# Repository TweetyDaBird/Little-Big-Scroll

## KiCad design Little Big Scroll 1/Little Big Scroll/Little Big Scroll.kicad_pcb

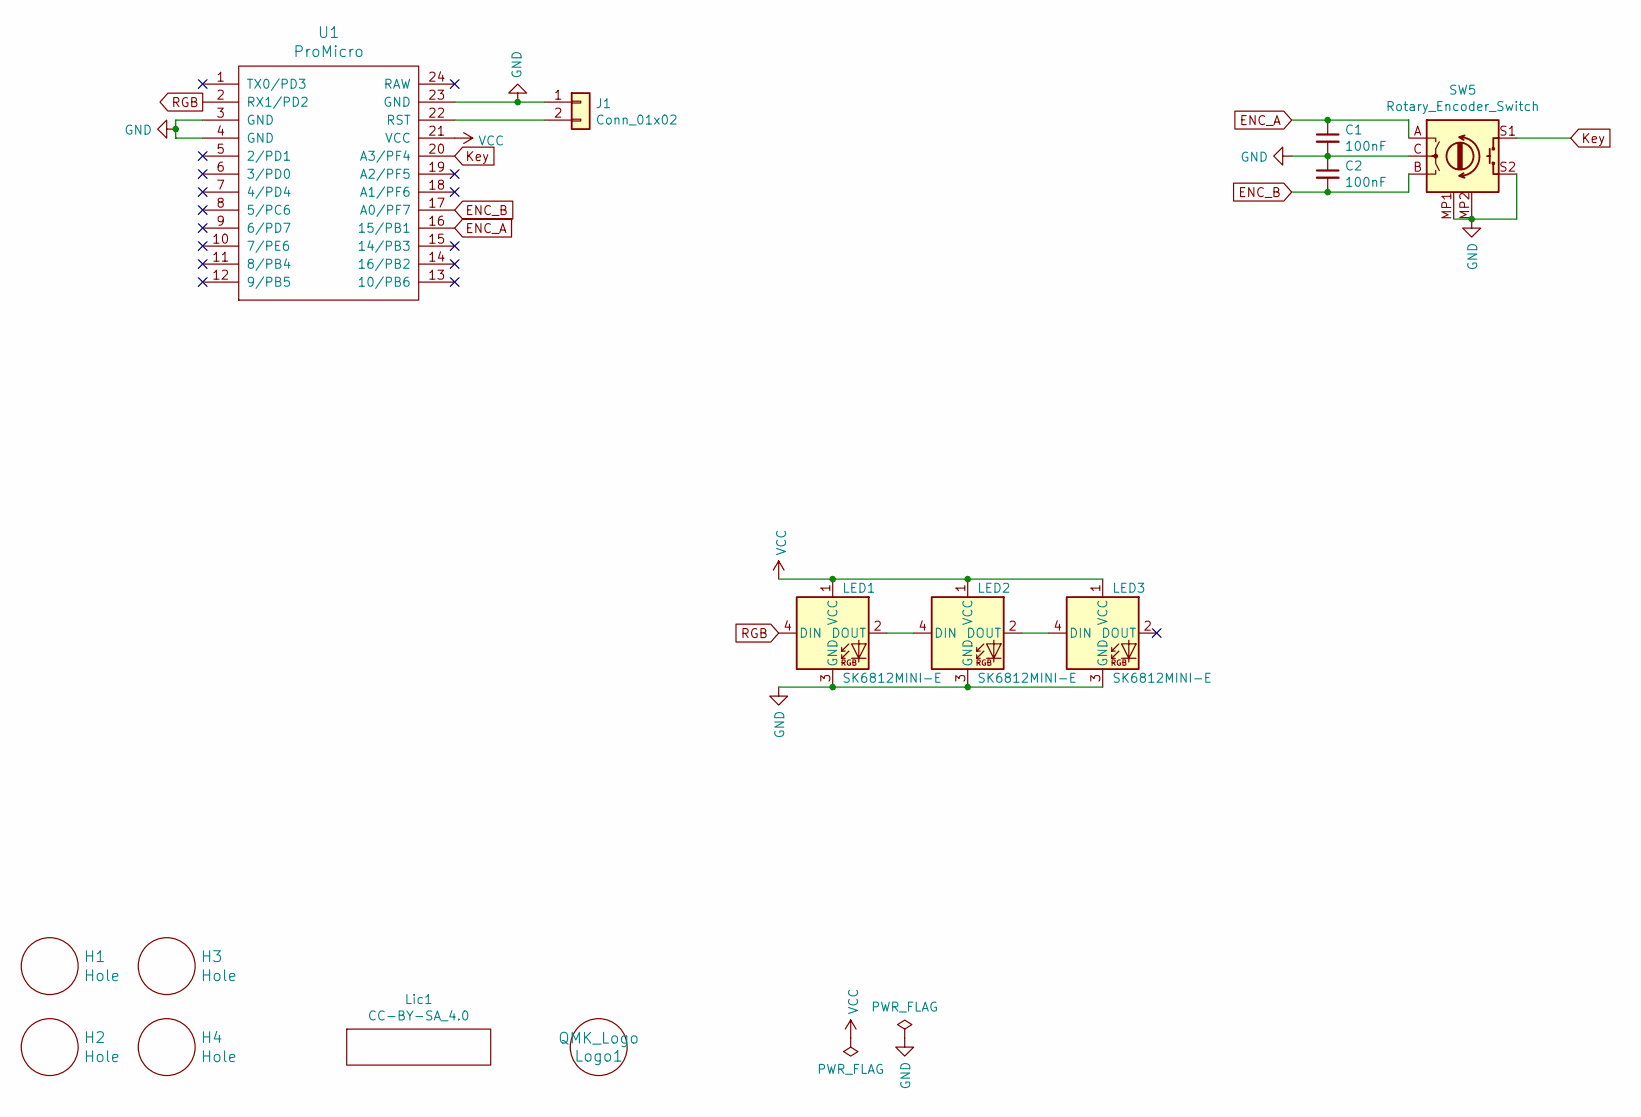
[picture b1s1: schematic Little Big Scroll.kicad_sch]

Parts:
C1, C2: 100nF; R_Axial_DIN0204_L3.6mm_D1.6mm_P5.08mm_Horizontal
H1, H2, H3, H4: Hole; MountingHole_3.7mm
J1: Conn_01x02; PinHeader_1x02_P2.54mm_Vertical
LED1, LED2, LED3: SK6812MINI-E; MX_SK6812MINI-E
Lic1: CC-BY-SA_4.0; CC_BY_SA_40
Logo1: QMK_Logo; Powered_by_QMK
SW5: Rotary_Encoder_Switch; RotaryEncoder_Alps_EC11E-Switch_Vertical_H20mm
U1: ProMicro; ArduinoProMicro-BackSide

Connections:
ENC_A: C1.1, SW5.A, U1.16 (15/PB1)
ENC_B: C2.2, SW5.B, U1.17 (A0/PF7)
GND: C1.2, C2.1, J1.1, LED1.3 (GND), LED2.3 (GND), LED3.3 (GND), SW5.C, SW5.MP1 (GND), SW5.MP2 (GND), SW5.S2, U1.3 (GND), U1.4 (GND), U1.23 (GND)
Key: SW5.S1, U1.20 (A3/PF4)
unnamed: J1.2, U1.22 (RST)
unnamed: LED1.2 (DOUT), LED2.4 (DIN)
unnamed: LED2.2 (DOUT), LED3.4 (DIN)
RGB: LED1.4 (DIN), U1.2 (RX1/PD2)
VCC: LED1.1 (VCC), LED2.1 (VCC), LED3.1 (VCC), U1.21 (VCC)

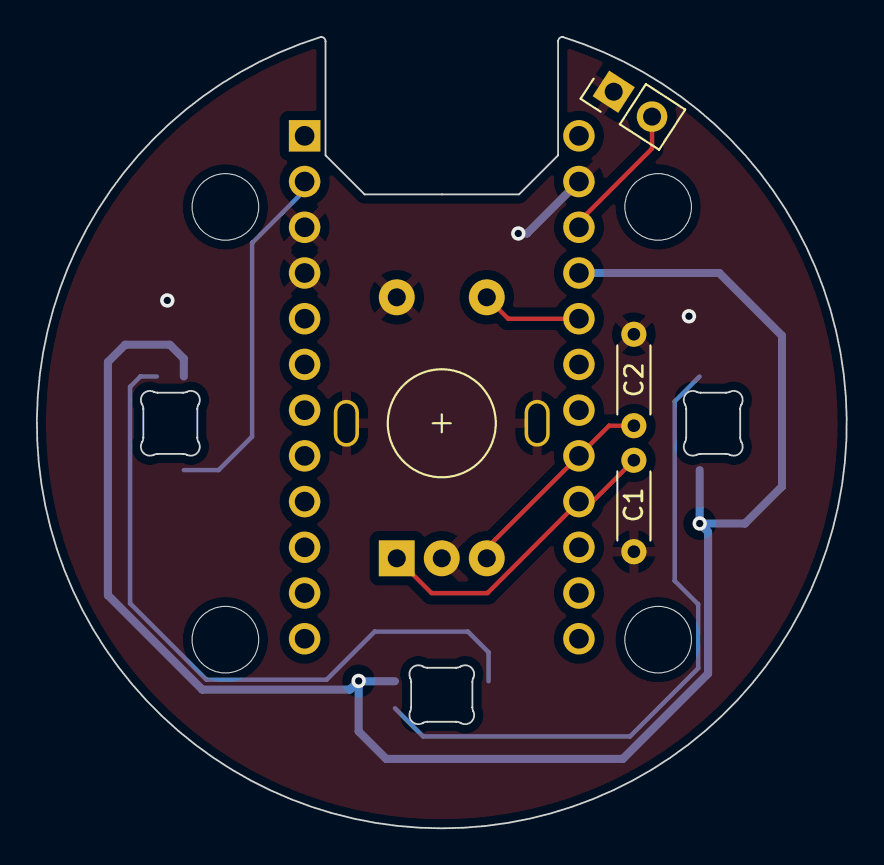
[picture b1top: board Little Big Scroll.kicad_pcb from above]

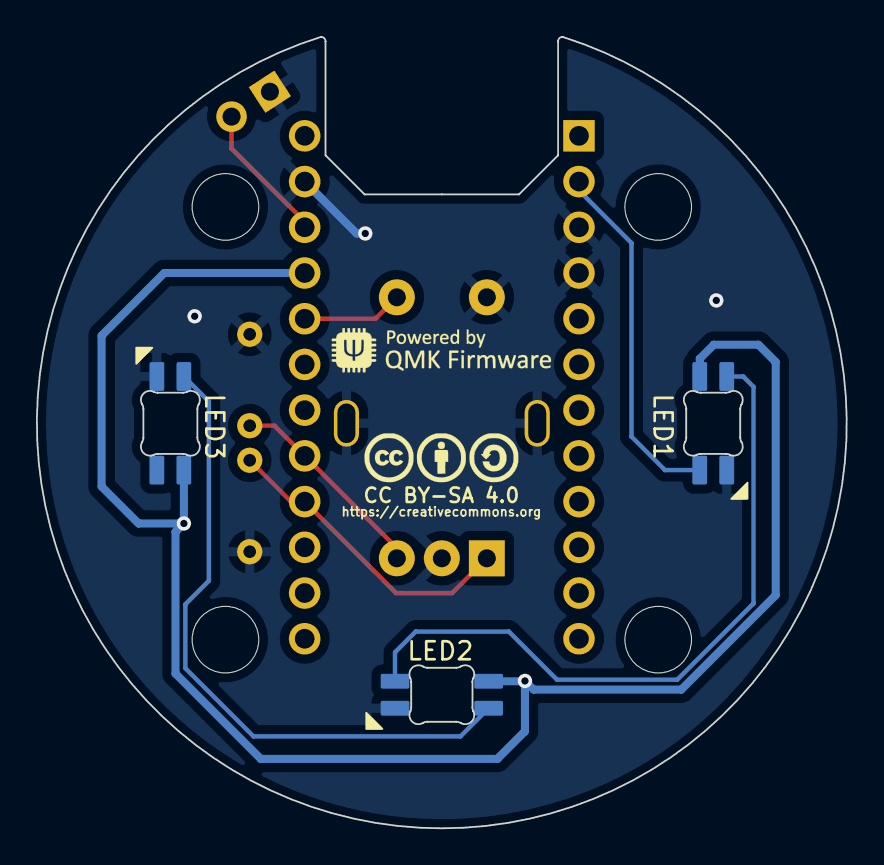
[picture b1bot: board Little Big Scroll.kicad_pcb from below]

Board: 2 copper layers, 45.0 x 44.0 mm, 14 parts (2 on the bottom side), 9 nets.

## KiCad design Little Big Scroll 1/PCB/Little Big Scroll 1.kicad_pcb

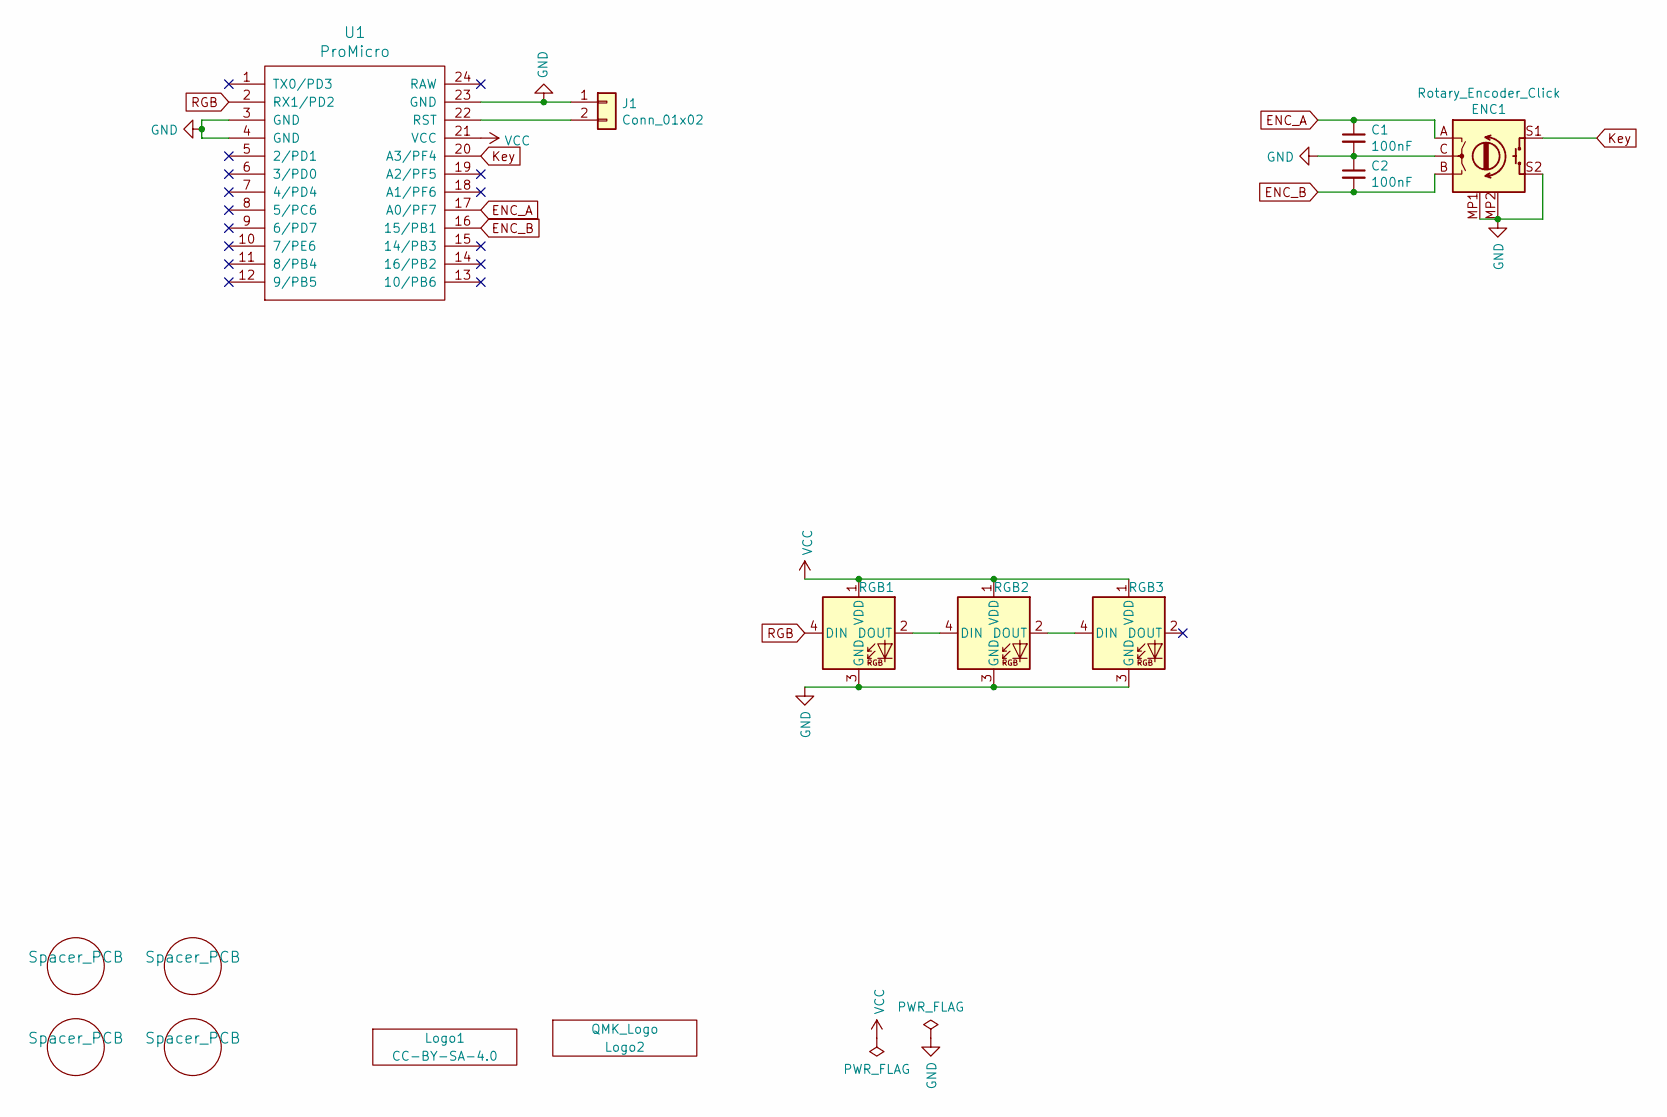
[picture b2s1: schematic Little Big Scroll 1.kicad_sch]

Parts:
C1, C2: 100nF; R_Axial_DIN0204_L3.6mm_D1.6mm_P5.08mm_Horizontal
ENC1: Rotary_Encoder_Click; Encoder_Alps_EC11E
H1, H2, H3, H4: Spacer_PCB; Spacer PCB hole
J1: Conn_01x02; SolderJumper-2_P1.3mm_Open_Pad1.0x1.5mm
Logo1: CC-BY-SA-4.0; CC_BY_SA_40
Logo2: QMK_Logo; Powered_by_QMK
RGB1, RGB2, RGB3: SK6812MINI-E; RGB_SK6812MINI-E
U1: ProMicro

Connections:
ENC_A: C1.1, ENC1.A, U1.17 (A0/PF7); also elsewhere on the board
ENC_B: C2.2, ENC1.B, U1.16 (15/PB1); also elsewhere on the board
GND: C1.2, C2.1, ENC1.C, ENC1.MP1 (GND), ENC1.MP2 (GND), ENC1.S2, J1.1, RGB1.3 (GND), RGB2.3 (GND), RGB3.3 (GND), U1.3 (GND), U1.4 (GND), U1.23 (GND); also elsewhere on the board
Key: ENC1.S1, U1.20 (A3/PF4); also elsewhere on the board
unnamed: J1.2, U1.22 (RST)
unnamed: RGB1.2 (DOUT), RGB2.4 (DIN)
unnamed: RGB2.2 (DOUT), RGB3.4 (DIN)
RGB: RGB1.4 (DIN), U1.2 (RX1/PD2)
VCC: RGB1.1 (VDD), RGB2.1 (VDD), RGB3.1 (VDD), U1.21 (VCC)

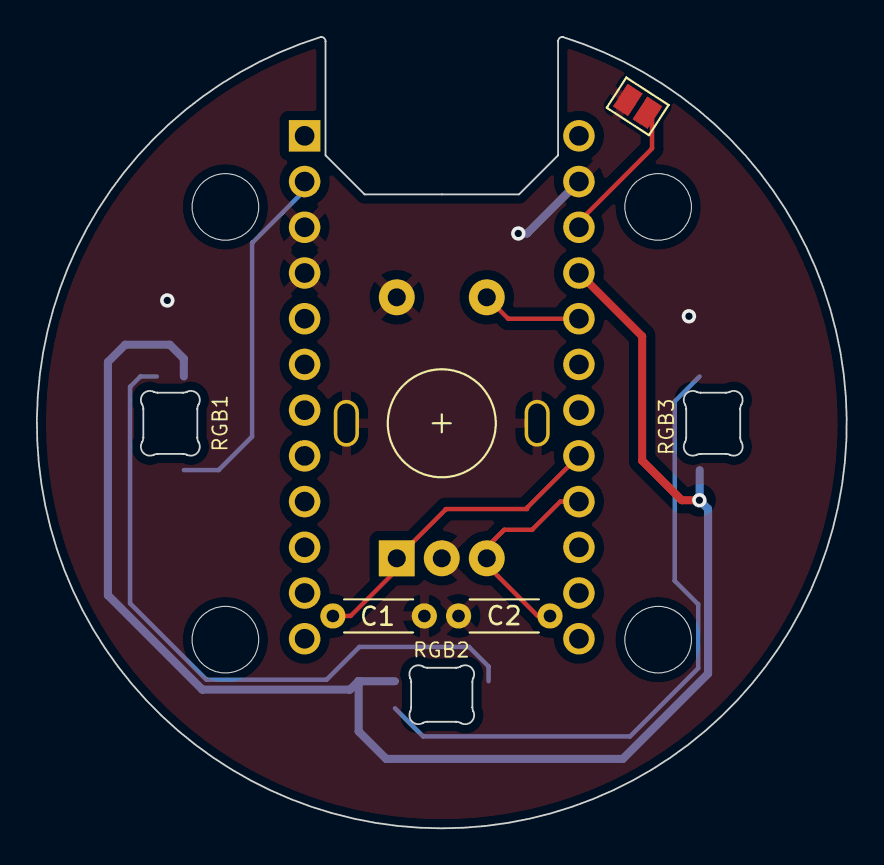
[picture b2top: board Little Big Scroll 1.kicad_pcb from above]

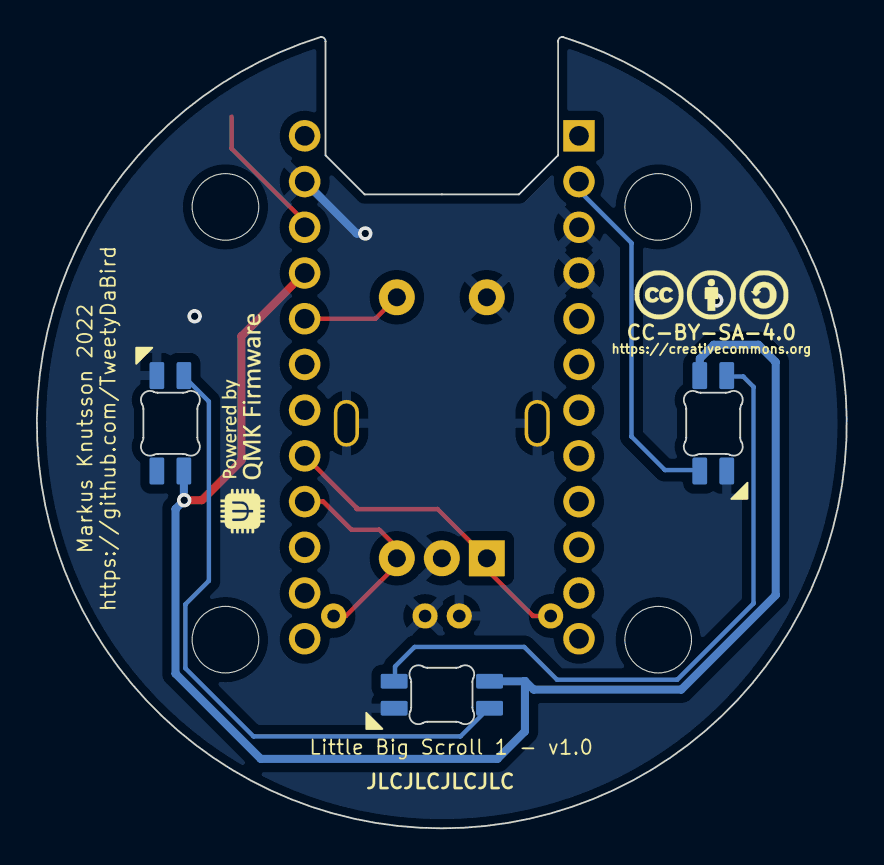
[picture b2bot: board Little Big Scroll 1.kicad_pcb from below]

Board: 2 copper layers, 45.0 x 44.0 mm, 14 parts (2 on the bottom side), 9 nets.

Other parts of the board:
SW5: Rotary_Encoder_Switch; RotaryEncoder_Alps_EC11E-Switch_Vertical_H20_special

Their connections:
ENC_A: SW5.A; also elsewhere on the board
ENC_B: SW5.B; also elsewhere on the board
GND: SW5.C, SW5.MP1 (GND), SW5.MP2 (GND), SW5.S2; also elsewhere on the board
Key: SW5.S1; also elsewhere on the board

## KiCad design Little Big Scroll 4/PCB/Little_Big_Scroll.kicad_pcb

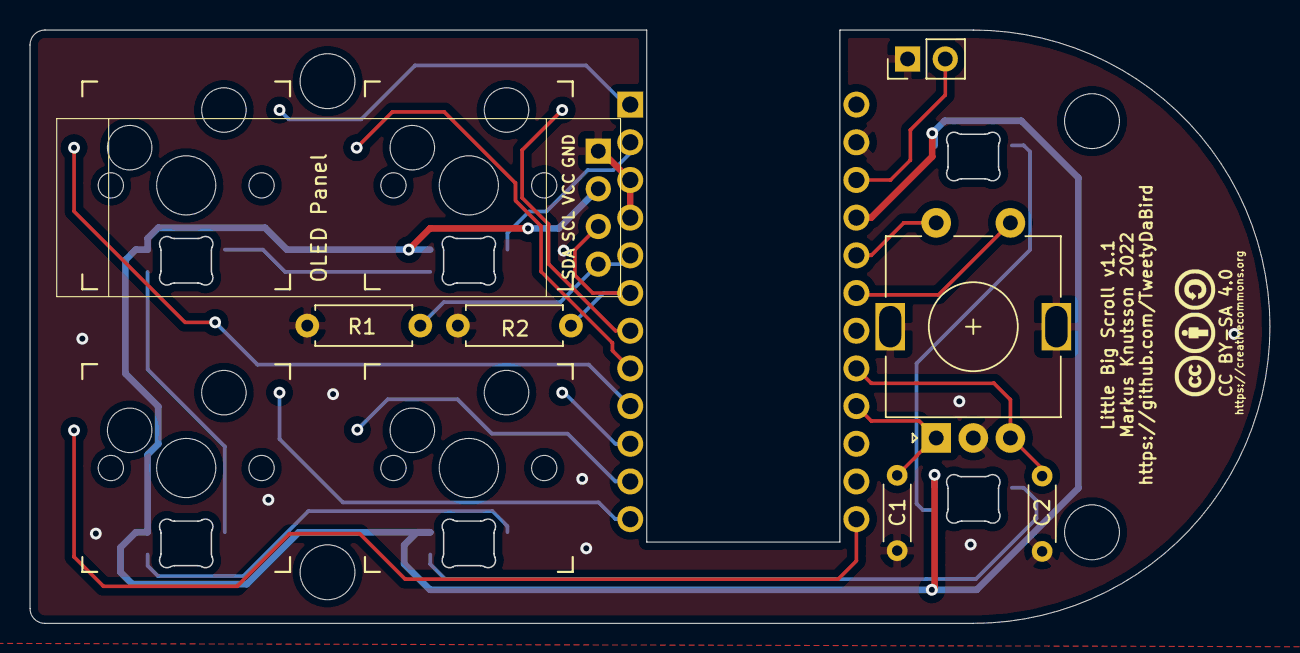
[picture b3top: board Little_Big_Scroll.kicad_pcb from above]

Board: 2 copper layers, 83.6 x 40.0 mm, 23 parts (0 on the bottom side), 23 nets.

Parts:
C1, C2: 100nF; R_Axial_DIN0204_L3.6mm_D1.6mm_P5.08mm_Horizontal
H1, H2, H3, H4: Hole; MountingHole_3.7mm
J1: Conn_01x02; PinHeader_1x02_P2.54mm_Vertical
LED1, LED2, LED3, LED4, LED5, LED6: SK6812MINI-E; MX_SK6812MINI-E
Lic1: CC-BY-SA_4.0; CC_BY_SA_40
OLED1: OLED_4pin; SSD1306-0.91-OLED-4pin-128x32
R1, R2: 4K7; R_Axial_DIN0207_L6.3mm_D2.5mm_P7.62mm_Horizontal
SW1, SW2, SW3, SW4: SW_Push; Kailh_socket_MX_RGB
SW5: Rotary_Encoder_Switch; RotaryEncoder_Alps_EC11E-Switch_Vertical_H20mm
U1: ProMicro; ArduinoProMicro-BackSide

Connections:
COL0: SW1.2, U1.9
COL1: SW2.2, U1.8
COL2: SW3.2, U1.13
COL3: SW4.2, U1.11
COL4: SW5.S1, U1.19
ENC_A: C1.1, SW5.A, U1.16
ENC_B: C2.2, SW5.B, U1.17
GND: C1.2, C2.1, J1.1, LED1.3, LED2.3, LED3.3, LED4.3, LED5.3, LED6.3, OLED1.1, R1.2, R2.2, SW5.C, SW5.MP1, SW5.MP2, U1.3, U1.4, U1.23
unnamed: J1.2, U1.22
unnamed: LED1.2, LED2.4
unnamed: LED2.2, LED3.4
unnamed: LED3.2, LED4.4
unnamed: LED4.2, LED5.4
unnamed: LED5.2, LED6.4
RGB: LED1.4, U1.2
ROW0: SW1.1, U1.1
ROW1: SW2.1, U1.7
ROW2: SW3.1, U1.12
ROW3: SW4.1, U1.10
ROW4: SW5.S2, U1.20
SCL: OLED1.3, R2.1, U1.6
SDA: OLED1.4, R1.1, U1.5
VCC: LED1.1, LED2.1, LED3.1, LED4.1, LED5.1, LED6.1, OLED1.2, U1.21

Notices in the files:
Little Big Scroll 1/PCB/Little Big Scroll 1.kicad_pcb:
Licensed under Creative Commons BY-SA 4.0 International
Little Big Scroll 4/PCB/Little_Big_Scroll.kicad_pcb:
Licensed under Creative Commons Attribution-ShareAlike 4.0 International
